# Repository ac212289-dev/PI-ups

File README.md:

Designed a UPS PCB using 18650 batteries

Integrated charging, protection, and USB I/O

Focused on efficient power routing and compact layout

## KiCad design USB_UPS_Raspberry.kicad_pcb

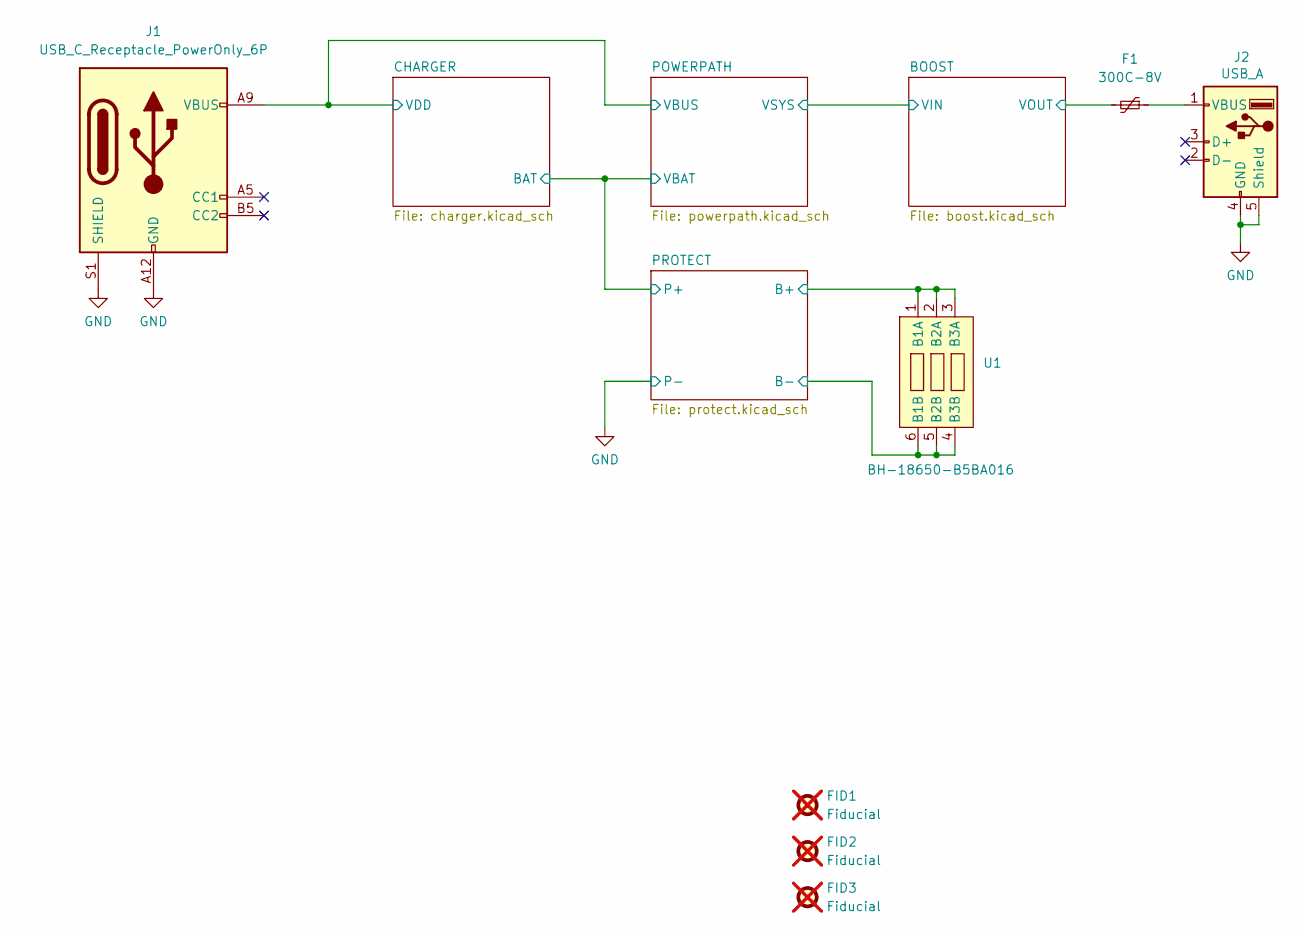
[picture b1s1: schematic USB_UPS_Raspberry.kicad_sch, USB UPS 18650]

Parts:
F1: 300C-8V; Fuse_1206_3216Metric; MPN# SMD1206-300C-8V
FID1, FID2, FID3: Fiducial; Fiducial_0.5mm_Mask1mm; not fitted
J1: USB_C_Receptacle_PowerOnly_6P; USB_C_Receptacle_HRO_TYPE-C-31-M-17; MPN# GT-USB-7002A
J2: USB_A; USB_A_Connfly_DS1095; MPN# DS1095-BNR0
U1: BH-18650-B5BA016; MPN# BH-18650-B5BA016

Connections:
/BOOST/VOUT: F1.2; also elsewhere on the board
/CHARGER/VDD: J1.A9 (VBUS), J1.B9 (VBUS); also elsewhere on the board
/PROTECT/B+: U1.1 (B1A), U1.2 (B2A), U1.3 (B3A); also elsewhere on the board
/PROTECT/B-: U1.4 (B3B), U1.5 (B2B), U1.6 (B1B); also elsewhere on the board
GND: J1.A12 (GND), J1.B12 (GND), J1.S1 (SHIELD), J2.4 (GND), J2.5 (Shield); also elsewhere on the board
unnamed: F1.1, J2.1 (VBUS)

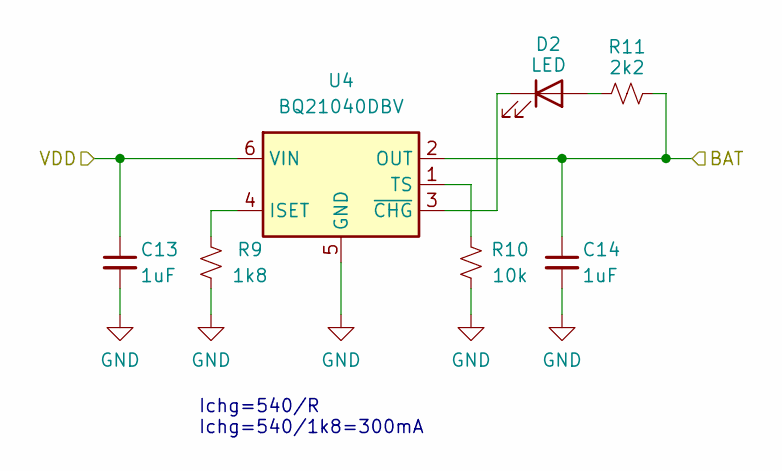
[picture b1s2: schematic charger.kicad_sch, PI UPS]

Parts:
C13, C14: 1uF; C_0603_1608Metric; MPN# CC0603KRX5R8BB105
D2: LED; LED_0603_1608Metric; MPN# LTST-C193KSKT-5A
R9: 1k8; R_0603_1608Metric; MPN# RT0603BRD071K8L
R10: 10k; R_0603_1608Metric; MPN# RT0603BRD0710KL
R11: 2k2; R_0603_1608Metric; MPN# RT0603BRD072K2L
U4: BQ21040DBV; SOT-23-6; MPN# BQ21040DBVR

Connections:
/CHARGER/BAT: C14.1, R11.1, U4.2 (OUT); also elsewhere on the board
/CHARGER/VDD: C13.1, U4.6 (VIN); also elsewhere on the board
GND: C13.2, C14.2, R9.2, R10.2, U4.5 (GND); also elsewhere on the board
unnamed: D2.2 (A), R11.2
unnamed: D2.1 (K), U4.3 (~CHG)
unnamed: R9.1, U4.4 (ISET)
unnamed: R10.1, U4.1 (TS)

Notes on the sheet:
Ichg=540/R Ichg=540/1k8=300mA

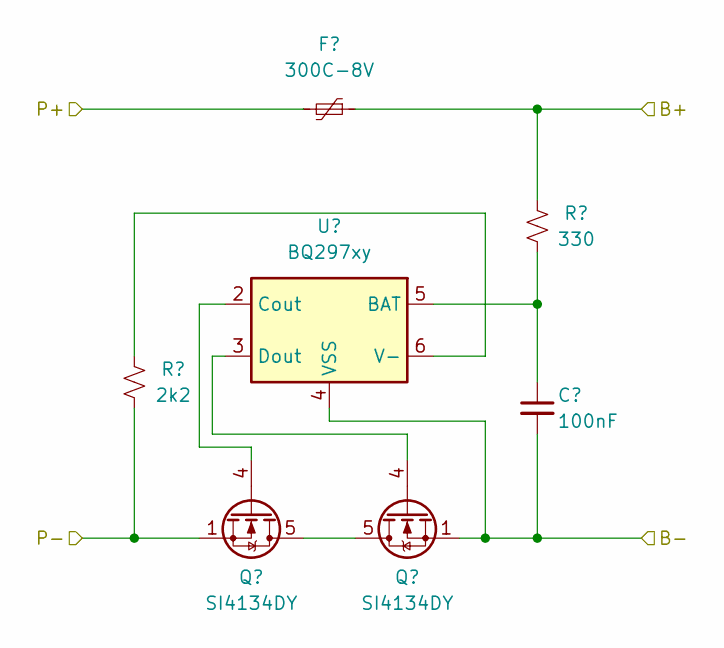
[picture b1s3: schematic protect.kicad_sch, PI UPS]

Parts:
C12: 100nF; C_0603_1608Metric; MPN# CC0603KRX7R8BB104
F2: 300C-8V; Fuse_1206_3216Metric; MPN# SMD1206-300C-8V
Q2, Q3: SI4134DY; SOIC-8_3.9x4.9mm_P1.27mm; MPN# SI4134DY-T1-GE3
R7: 2k2; R_0603_1608Metric; MPN# RT0603BRD072K2L
R8: 330; R_0603_1608Metric; MPN# RT0603BRE07330RL
U3: BQ297xy; WSON-6_1.5x1.5mm_P0.5mm; MPN# BQ29700DSER

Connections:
/CHARGER/BAT: F2.2; also elsewhere on the board
/PROTECT/B+: F2.1, R8.1; also elsewhere on the board
/PROTECT/B-: C12.2, Q3.1 (S), Q3.2 (S), Q3.3 (S), U3.4 (VSS); also elsewhere on the board
GND: Q2.1 (S), Q2.2 (S), Q2.3 (S), R7.2; also elsewhere on the board
unnamed: Q2.5 (D), Q2.6 (D), Q2.7 (D), Q2.8 (D), Q3.5 (D), Q3.6 (D), Q3.7 (D), Q3.8 (D)
unnamed: Q2.4 (G), U3.2 (Cout)
unnamed: Q3.4 (G), U3.3 (Dout)
unnamed: C12.1, R8.2, U3.5 (BAT)
unnamed: R7.1, U3.6 (V-)

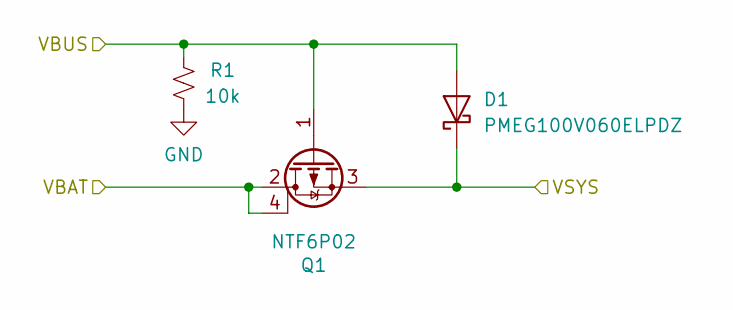
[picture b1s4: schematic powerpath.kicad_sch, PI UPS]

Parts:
D1: PMEG100V060ELPDZ; Nexperia_CFP15_SOT-1289; MPN# PMEG100V060ELPDZ
Q1: NTF6P02; SOT-223-3_TabPin2; MPN# NTF6P02T3G
R1: 10k; R_0603_1608Metric; MPN# RT0603BRD0710KL

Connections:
/BOOST/VIN: D1.3 (K), Q1.3 (S); also elsewhere on the board
/CHARGER/BAT: Q1.2 (D), Q1.4 (D); also elsewhere on the board
/CHARGER/VDD: D1.1 (A), D1.2 (A), Q1.1 (G), R1.1; also elsewhere on the board
GND: R1.2; also elsewhere on the board

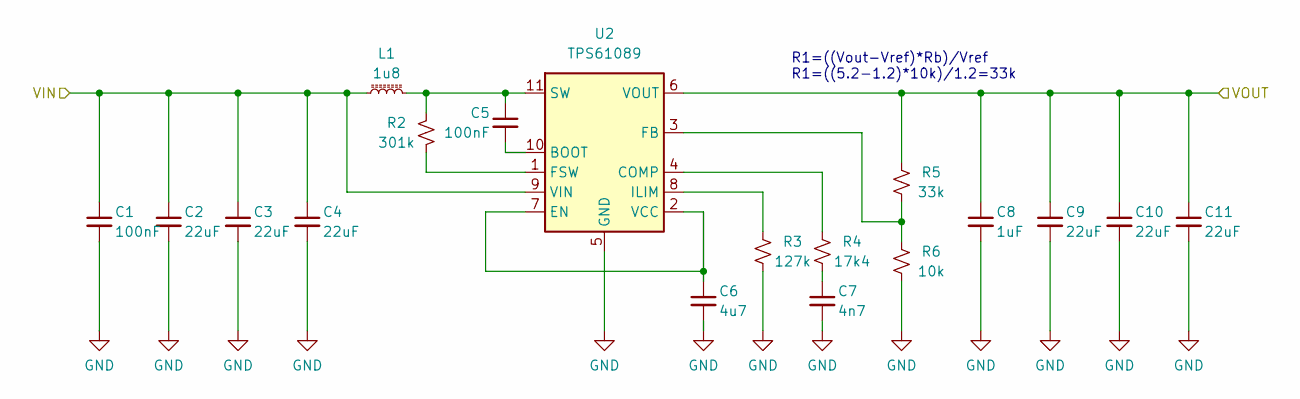
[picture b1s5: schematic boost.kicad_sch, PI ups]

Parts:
C1, C5: 100nF; C_0603_1608Metric; MPN# CC0603KRX7R8BB104
C2, C3, C4, C9, C10, C11: 22uF; C_0603_1608Metric; MPN# GRM188R61C226ME01D
C6: 4u7; C_0603_1608Metric; MPN# GRM188R61E475KE11D
C7: 4n7; C_0603_1608Metric; MPN# CC0603KRX7R8BB472
C8: 1uF; C_0603_1608Metric; MPN# CC0603KRX5R8BB105
L1: 1u8; L_Bourns_SRP6060FA; MPN# YSPIT0630A-1R8M
R2: 301k; R_0603_1608Metric; MPN# RT0603BRE07301KL
R3: 127k; R_0603_1608Metric; MPN# RT0603FRE07127KL
R4: 17k4; R_0603_1608Metric; MPN# RT0603BRD0717K4L
R5: 33k; R_0603_1608Metric; MPN# RT0603BRD0733KL
R6: 10k; R_0603_1608Metric; MPN# RT0603BRD0710KL
U2: TPS61089; Texas_VQFN-RNR0011A-11; MPN# TPS61089RNRR

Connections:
/BOOST/VIN: C1.1, C2.1, C3.1, C4.1, L1.1, U2.9 (VIN); also elsewhere on the board
/BOOST/VOUT: C8.1, C9.1, C10.1, C11.1, R5.1, U2.6 (VOUT); also elsewhere on the board
GND: C1.2, C2.2, C3.2, C4.2, C6.2, C7.2, C8.2, C9.2, C10.2, C11.2, R3.2, R6.2, U2.5 (GND); also elsewhere on the board
unnamed: C7.1, R4.2
unnamed: C5.2, U2.10 (BOOT)
unnamed: R4.1, U2.4 (COMP)
unnamed: C6.1, U2.2 (VCC), U2.7 (EN)
unnamed: R5.2, R6.1, U2.3 (FB)
unnamed: R2.2, U2.1 (FSW)
unnamed: R3.1, U2.8 (ILIM)
unnamed: C5.1, L1.2, R2.1, U2.11 (SW)

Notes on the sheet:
R1=((Vout-Vref)*Rb)/Vref R1=((5.2-1.2)*10k)/1.2=33k

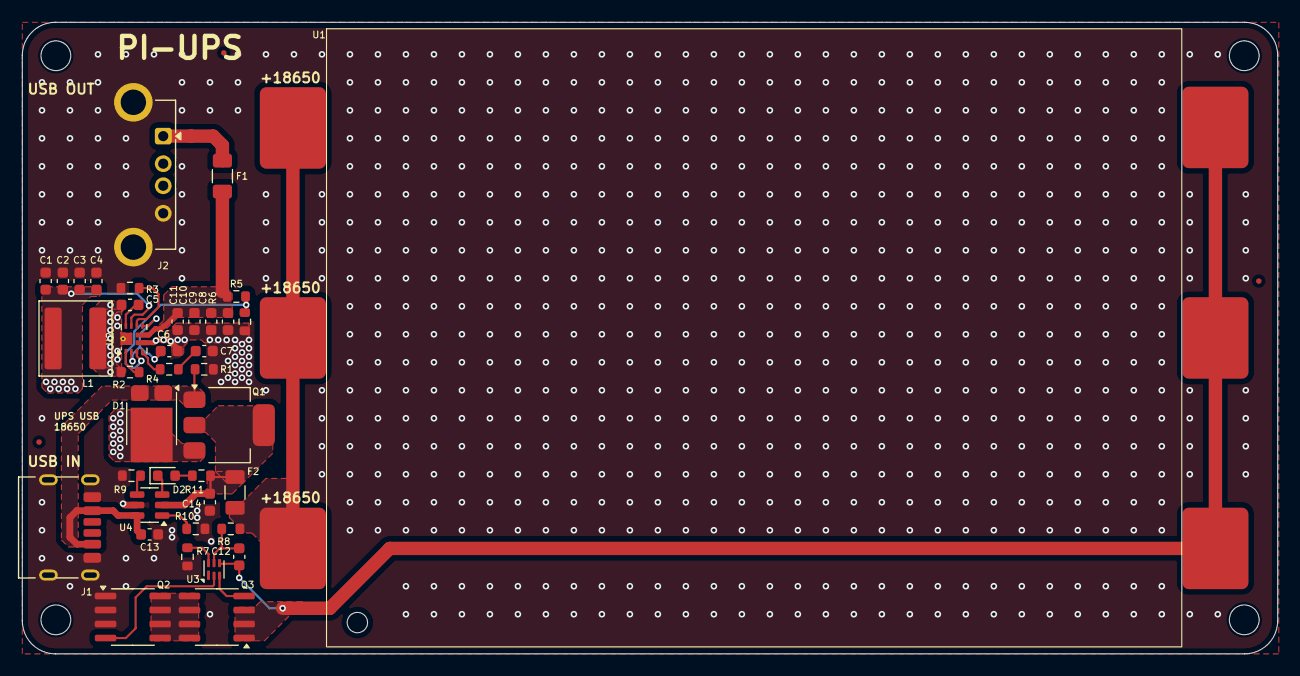
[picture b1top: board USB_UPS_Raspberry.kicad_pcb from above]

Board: 2 copper layers, 113.9 x 57.3 mm, 42 parts (0 on the bottom side), 25 nets.

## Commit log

2026-04-15 Add project description for UPS PCB design
